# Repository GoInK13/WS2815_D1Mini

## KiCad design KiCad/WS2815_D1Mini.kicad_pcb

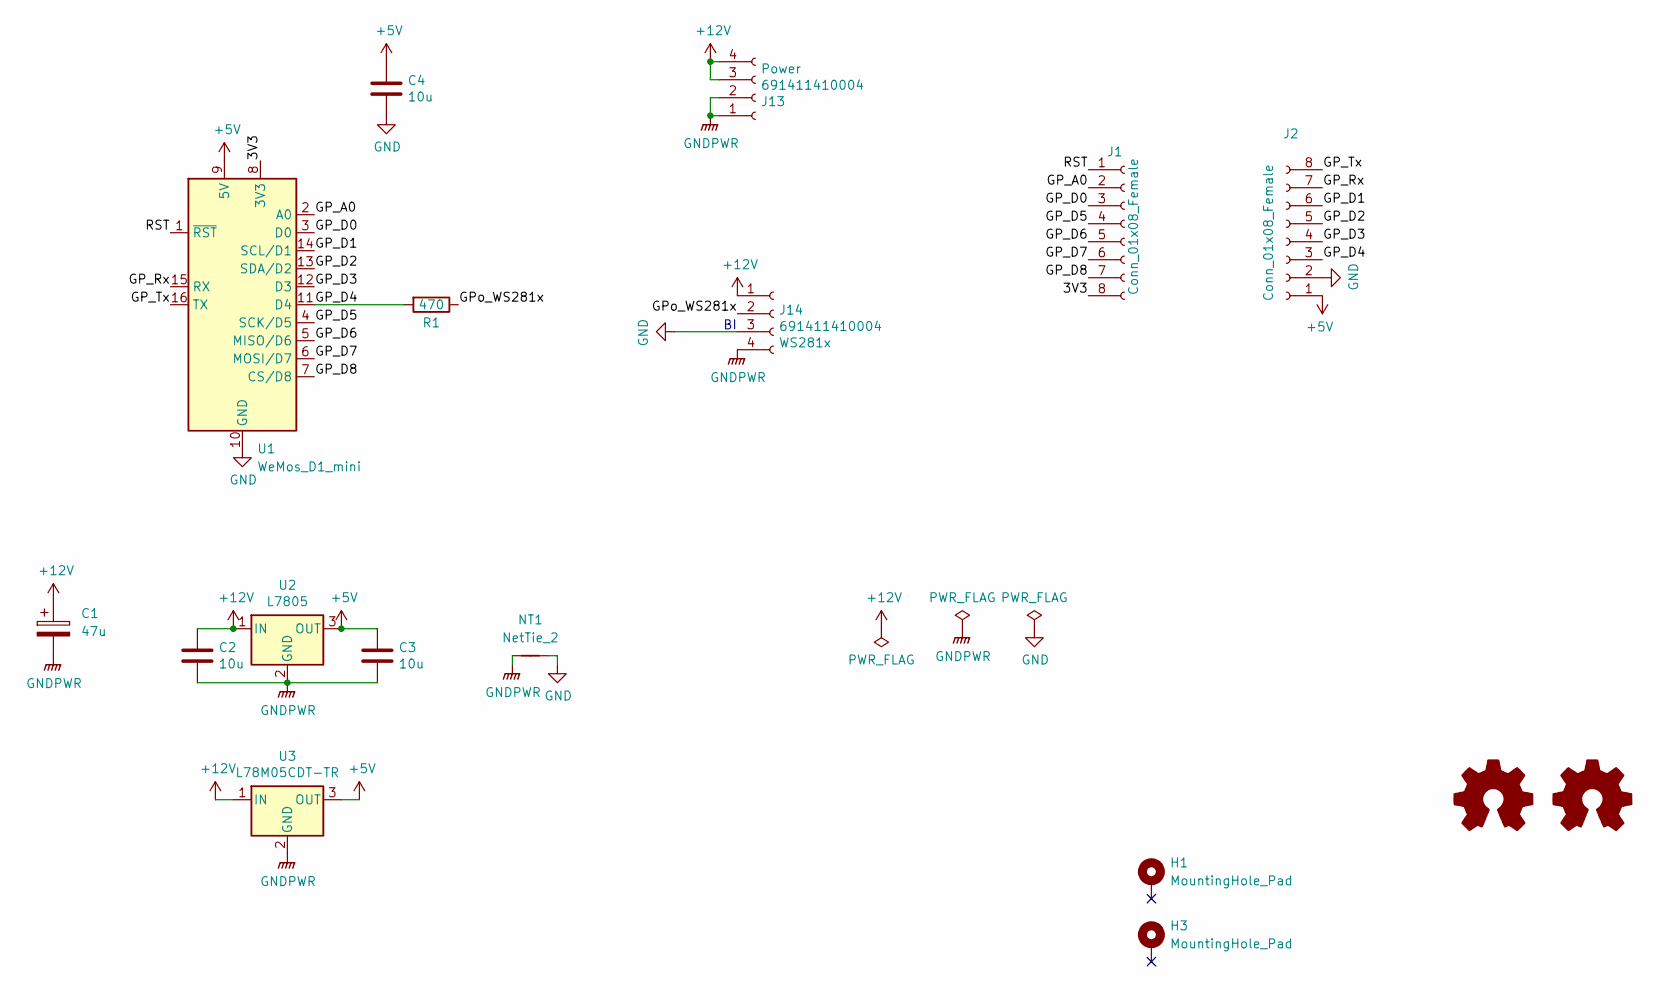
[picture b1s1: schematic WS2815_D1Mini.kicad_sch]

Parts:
C1: 47u; CP_Radial_D5.0mm_P2.00mm
C2, C3, C4: 10u; C_1206_3216Metric
H1, H3: MountingHole_Pad; MountingHole_4.3mm_M4_DIN965_Pad
J1, J2: Conn_01x08_Female; PinHeader_1x08_P2.54mm_Vertical
J13, J14: 691411410004; WR-TBL-7.62mm-4P_691411410004
LOGO1: Logo_Open_Hardware_Large; GoInK600
LOGO2: Logo_Open_Hardware_Large; GoInK400
NT1: NetTie_2; NetTie-2_SMD_Pad0.5mm
R1: 470; R_0603_1608Metric
U1: WeMos_D1_mini; WEMOS_D1_mini_light
U2: L7805; TO-220-3_Horizontal_TabDown
U3: L78M05CDT-TR; TO-252-2; LCSC C55509

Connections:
+5V: C3.1, C4.1, J2.1, U1.9 (5V), U2.3 (OUT), U3.3 (OUT)
+12V: C1.1, C2.1, J13.3, J13.4, J14.1, U2.1 (IN), U3.1 (IN)
/3V3: J1.8, U1.8 (3V3)
/GP_A0: J1.2, U1.2 (A0)
/GP_D0: J1.3, U1.3 (D0)
/GP_D1: J2.6, U1.14 (SCL/D1)
/GP_D2: J2.5, U1.13 (SDA/D2)
/GP_D3: J2.4, U1.12 (D3)
/GP_D4: J2.3, R1.2, U1.11 (D4)
/GP_D5: J1.4, U1.4 (SCK/D5)
/GP_D6: J1.5, U1.5 (MISO/D6)
/GP_D7: J1.6, U1.6 (MOSI/D7)
/GP_D8: J1.7, U1.7 (CS/D8)
/GP_Rx: J2.7, U1.15 (RX)
/GP_Tx: J2.8, U1.16 (TX)
/GPo_WS281x: J14.2, R1.1
/RST: J1.1, U1.1 (~RST)
GND: C4.2, J2.2, J14.3, NT1.2, U1.10 (GND)
GNDPWR: C1.2, C2.2, C3.2, J13.1, J13.2, J14.4, NT1.1, U2.2 (GND), U3.2 (GND)

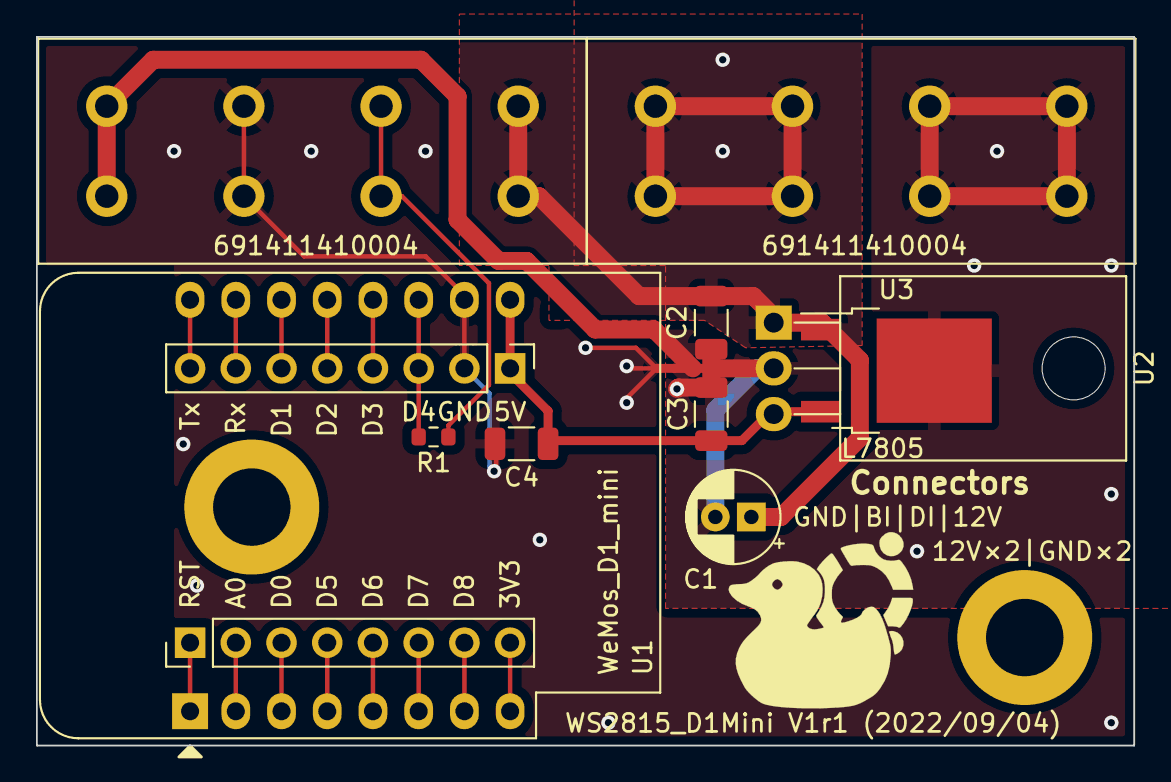
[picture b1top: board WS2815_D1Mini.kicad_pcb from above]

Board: 2 copper layers, 61.0 x 39.4 mm, 17 parts (1 on the bottom side), 19 nets.

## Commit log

2022-08-28 Init with first RC
2022-09-04 Add 2 mounting holes + move 12V and GND in power
2022-09-09 Add zip, bom and pos for jlc
2022-09-09 Remove backup
2022-11-10 Add strip_connector
